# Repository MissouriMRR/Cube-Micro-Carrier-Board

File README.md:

# Cube-Micro-Carrier-Board
Attempt at making a stacking Cube carrier board. The goal is to have the board be the same area as the cube

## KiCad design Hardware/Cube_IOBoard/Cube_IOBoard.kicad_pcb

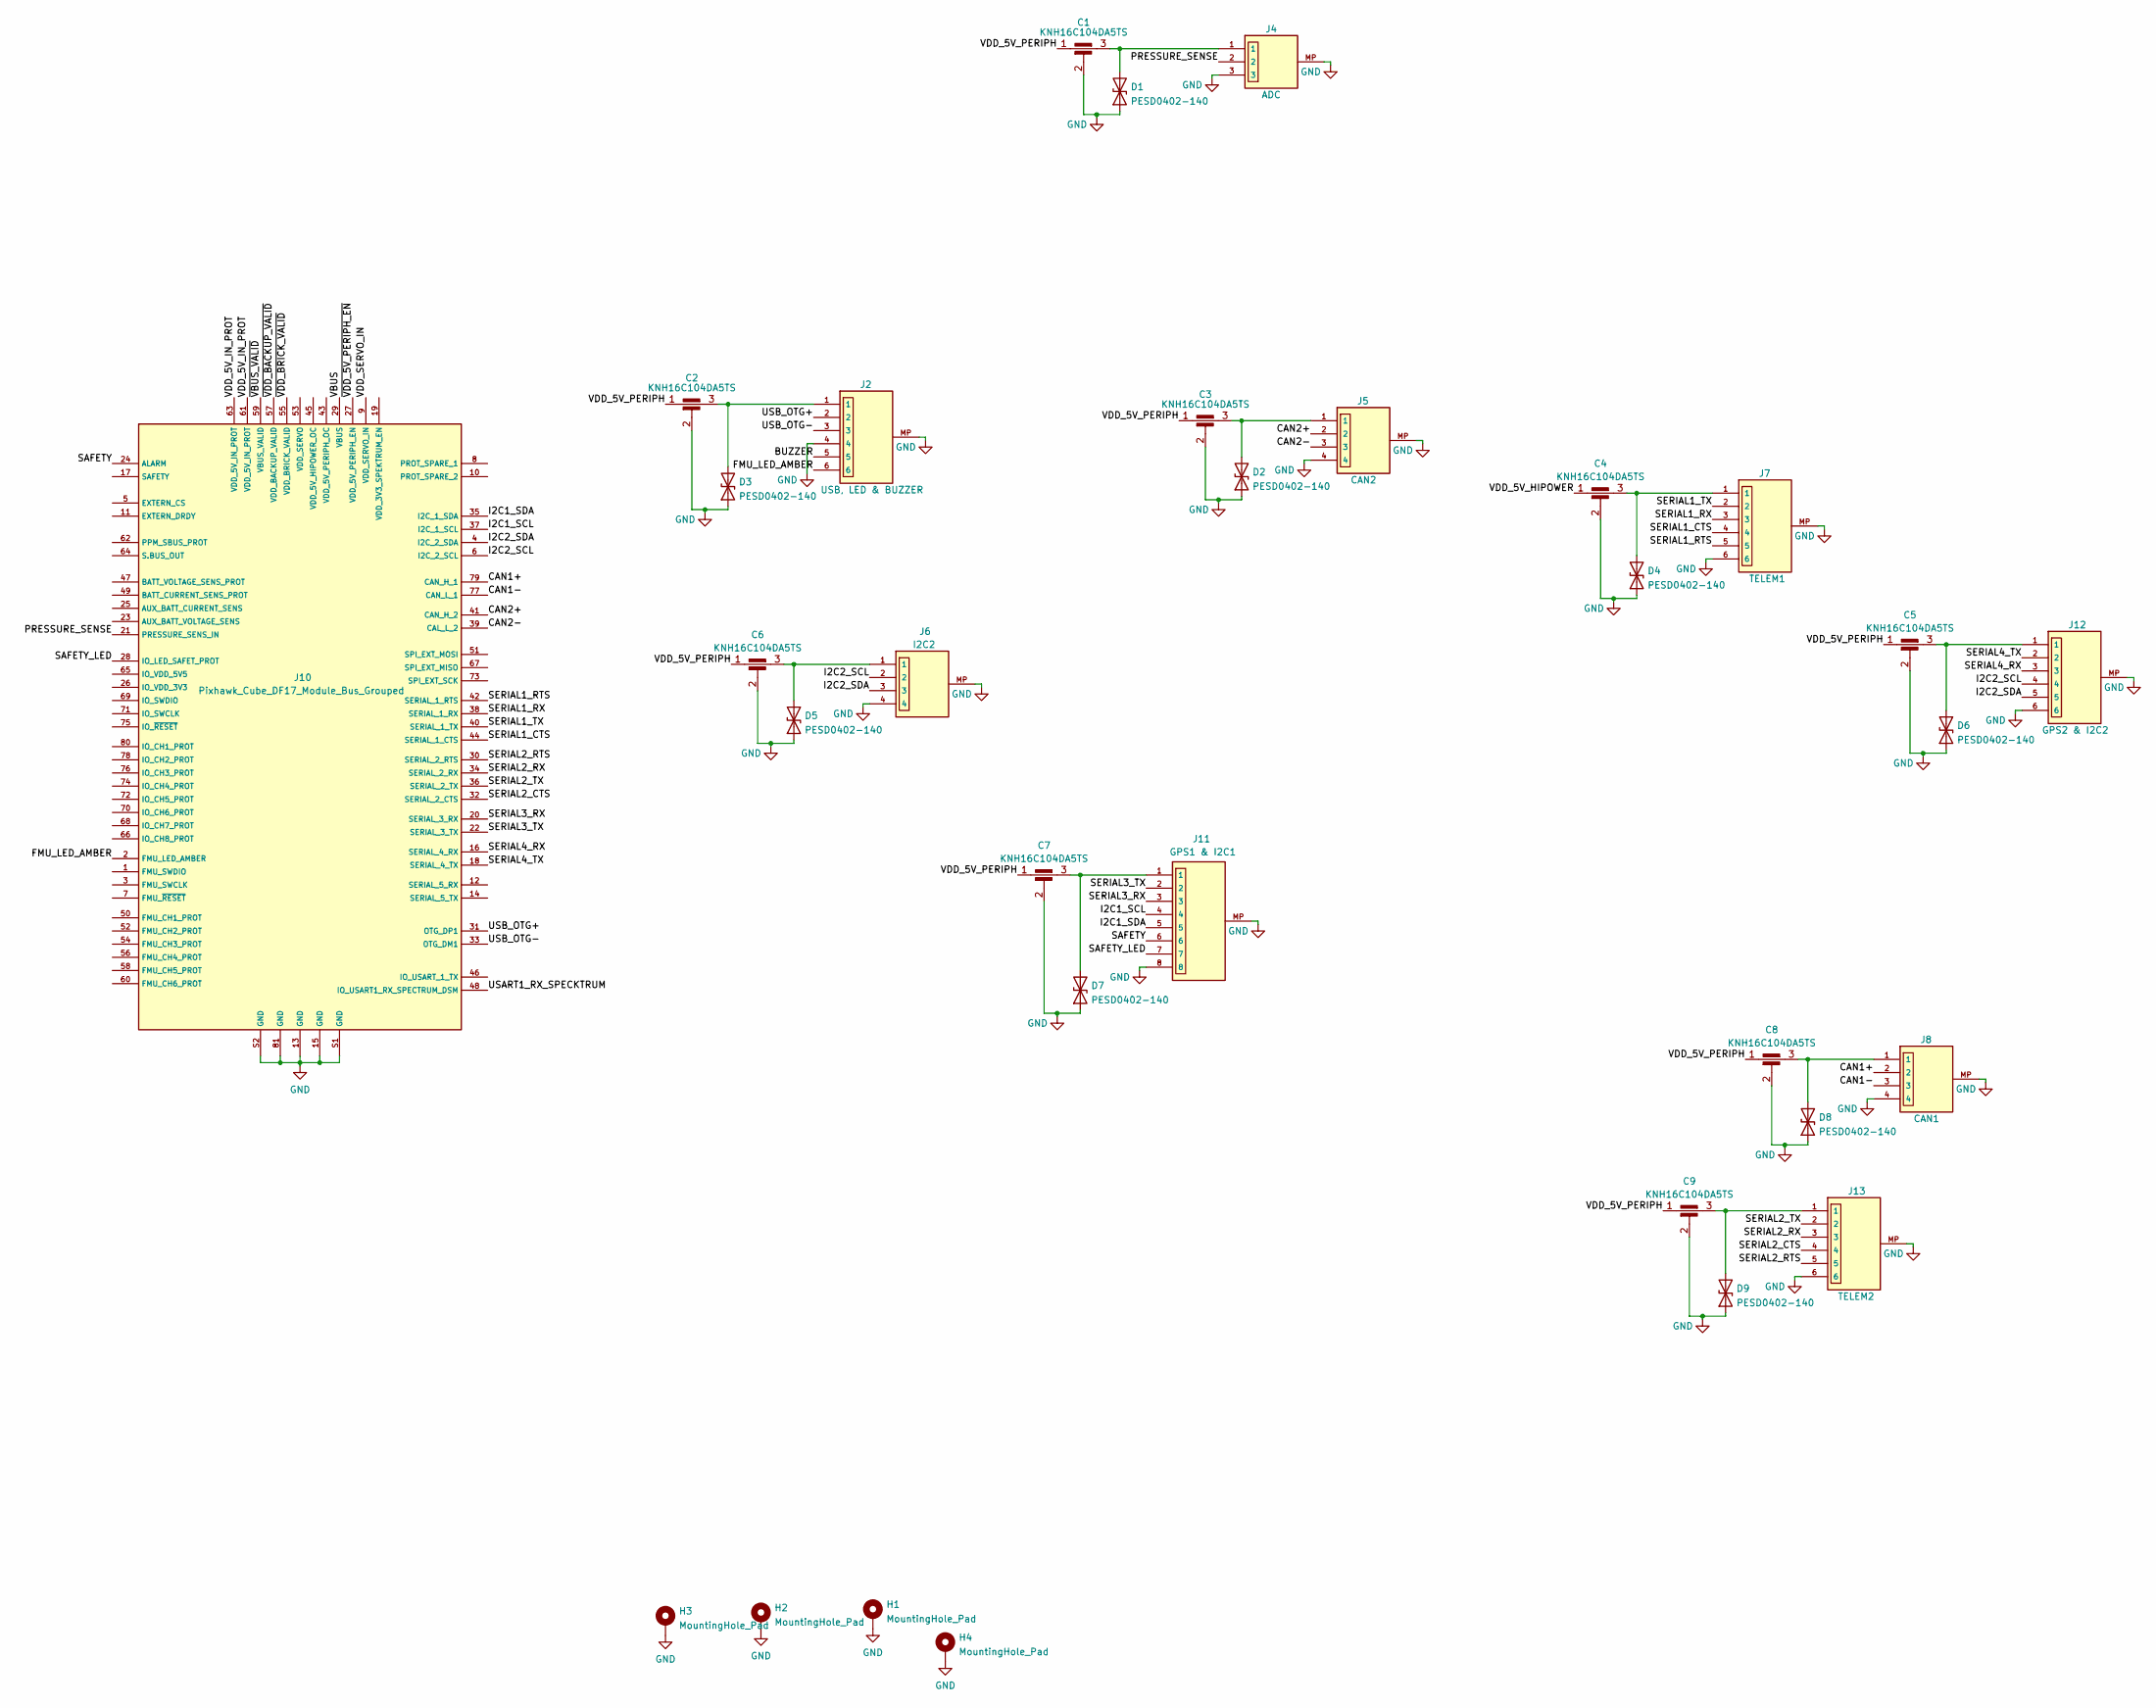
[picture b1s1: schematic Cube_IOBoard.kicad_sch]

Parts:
C1, C2, C3, C4, C5, C6, C7, C8, C9: KNH16C104DA5TS
D1, D2, D3, D4, D5, D6, D7, D8, D9: PESD0402-140; D_0402_1005Metric
H1, H2, H3, H4: MountingHole_Pad; MountingHole_3.2mm_M3_DIN965_Pad
J2: USB, LED & BUZZER; JST_GH_SM06B-GHS-TB_1x06-1MP_P1.25mm_Horizontal; PARTREV N/A
J4: ADC; JST_GH_SM03B-GHS-TB_1x03-1MP_P1.25mm_Horizontal
J5: CAN2; JST_GH_SM04B-GHS-TB_1x04-1MP_P1.25mm_Horizontal; PARTREV N/A
J6: I2C2; JST_GH_SM04B-GHS-TB_1x04-1MP_P1.25mm_Horizontal; PARTREV N/A
J7: TELEM1; JST_GH_SM06B-GHS-TB_1x06-1MP_P1.25mm_Horizontal; PARTREV N/A
J8: CAN1; JST_GH_SM04B-GHS-TB_1x04-1MP_P1.25mm_Horizontal; PARTREV N/A
J10: Pixhawk_Cube_DF17_Module_Bus_Grouped; Cube_DF17_Module_Bus
J11: GPS1 & I2C1; JST_GH_SM08B-GHS-TB_1x08-1MP_P1.25mm_Horizontal
J12: GPS2 & I2C2; JST_GH_SM06B-GHS-TB_1x06-1MP_P1.25mm_Horizontal; PARTREV N/A
J13: TELEM2; JST_GH_SM06B-GHS-TB_1x06-1MP_P1.25mm_Horizontal; PARTREV N/A

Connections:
/BUZZER: J2.5
/CAN1+: J8.2, J10.79 (CAN_H_1)
/CAN1-: J8.3, J10.77 (CAN_L_1)
/CAN2+: J5.2, J10.41 (CAN_H_2)
/CAN2-: J5.3, J10.39 (CAL_L_2)
/FMU_LED_AMBER: J2.6, J10.2 (FMU_LED_AMBER)
/I2C1_SCL: J10.37 (I2C_1_SCL), J11.4
/I2C1_SDA: J10.35 (I2C_1_SDA), J11.5
/I2C2_SCL: J6.2, J10.6 (I2C_2_SCL), J12.4
/I2C2_SDA: J6.3, J10.4 (I2C_2_SDA), J12.5
/PRESSURE_SENSE: J4.2, J10.21 (PRESSURE_SENS_IN)
/SAFETY: J10.24 (ALARM), J11.6
/SAFETY_LED: J10.28 (IO_LED_SAFET_PROT), J11.7
/SERIAL1_CTS: J7.4, J10.44 (SERIAL_1_CTS)
/SERIAL1_RTS: J7.5, J10.42 (SERIAL_1_RTS)
/SERIAL1_RX: J7.3, J10.38 (SERIAL_1_RX)
/SERIAL1_TX: J7.2, J10.40 (SERIAL_1_TX)
/SERIAL2_CTS: J10.32 (SERIAL_2_CTS), J13.4
/SERIAL2_RTS: J10.30 (SERIAL_2_RTS), J13.5
/SERIAL2_RX: J10.34 (SERIAL_2_RX), J13.3
/SERIAL2_TX: J10.36 (SERIAL_2_TX), J13.2
/SERIAL3_RX: J10.20 (SERIAL_3_RX), J11.3
/SERIAL3_TX: J10.22 (SERIAL_3_TX), J11.2
/SERIAL4_RX: J10.16 (SERIAL_4_RX), J12.3
/SERIAL4_TX: J10.18 (SERIAL_4_TX), J12.2
/USART1_RX_SPECKTRUM: J10.48 (IO_USART1_RX_SPECTRUM_DSM)
/USB_OTG+: J2.2, J10.31 (OTG_DP1)
/USB_OTG-: J2.3, J10.33 (OTG_DM1)
/VBUS: J10.29 (VBUS)
/VDD_5V_HIPOWER: C4.1
/VDD_5V_IN_PROT: J10.61 (VDD_5V_IN_PROT), J10.63 (VDD_5V_IN_PROT)
/VDD_5V_PERIPH: C1.1, C2.1, C3.1, C5.1, C6.1, C7.1, C8.1, C9.1
/VDD_SERVO_IN: J10.9 (VDD_SERVO_IN)
/~VBUS_VALID: J10.59 (VBUS_VALID)
/~VDD_5V_PERIPH_EN: J10.27 (VDD_5V_PERIPH_EN)
/~VDD_BACKUP_VALID: J10.57 (VDD_BACKUP_VALID)
/~VDD_BRICK_VALID: J10.55 (VDD_BRICK_VALID)
GND: C1.2, C2.2, C3.2, C4.2, C5.2, C6.2, C7.2, C8.2, C9.2, D1.1 (A1), D2.1 (A1), D3.1 (A1), D4.1 (A1), D5.1 (A1), D6.1 (A1), D7.1 (A1), D8.1 (A1), D9.1 (A1), H1.1, H2.1, H3.1, H4.1, J2.4, J2.MP, J4.3, J4.MP, J5.4, J5.MP, J6.4, J6.MP, J7.6, J7.MP, J8.4, J8.MP, J10.13 (GND), J10.15 (GND), J10.81 (GND), J10.S1 (GND), J10.S2 (GND), J11.8, J11.MP, J12.6, J12.MP, J13.6, J13.MP
unnamed: C2.3, D3.2 (A2), J2.1
unnamed: C1.3, D1.2 (A2), J4.1
unnamed: C3.3, D2.2 (A2), J5.1
unnamed: C6.3, D5.2 (A2), J6.1
unnamed: C4.3, D4.2 (A2), J7.1
unnamed: C8.3, D8.2 (A2), J8.1
unnamed: C7.3, D7.2 (A2), J11.1
unnamed: C5.3, D6.2 (A2), J12.1
unnamed: C9.3, D9.2 (A2), J13.1

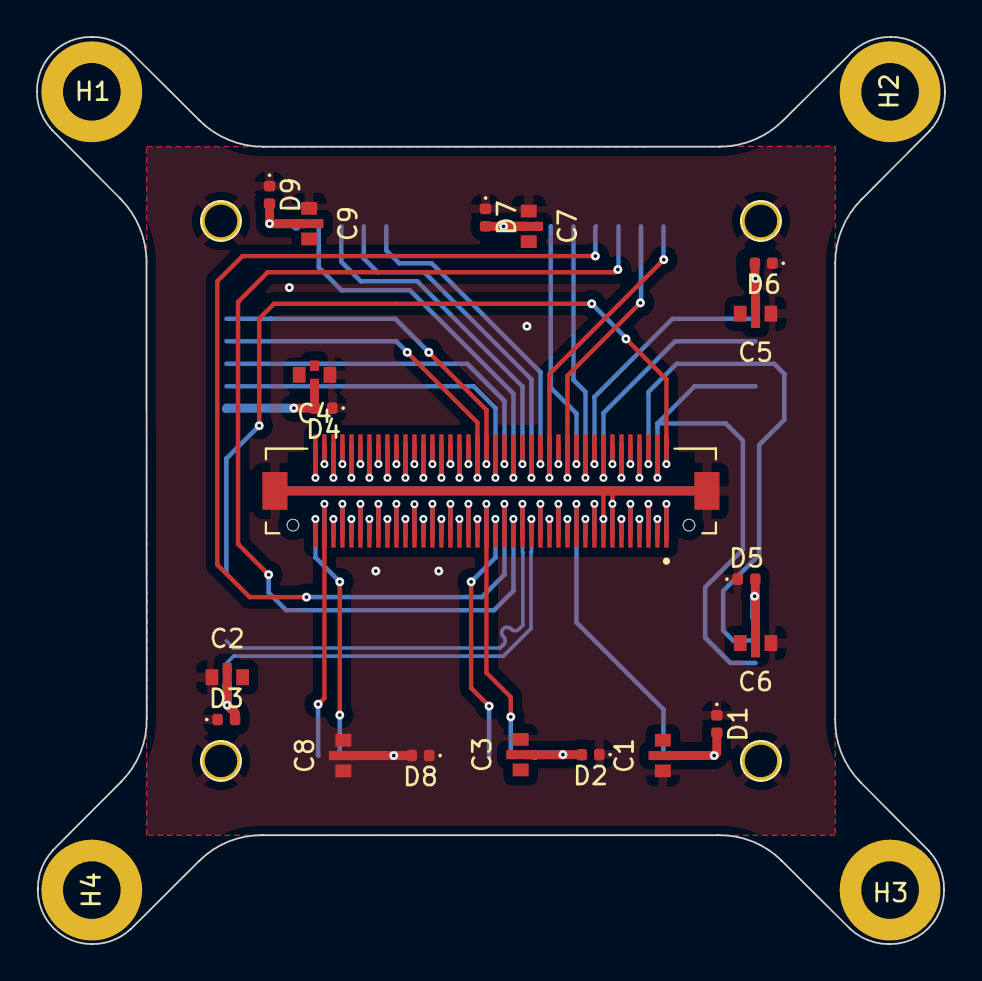
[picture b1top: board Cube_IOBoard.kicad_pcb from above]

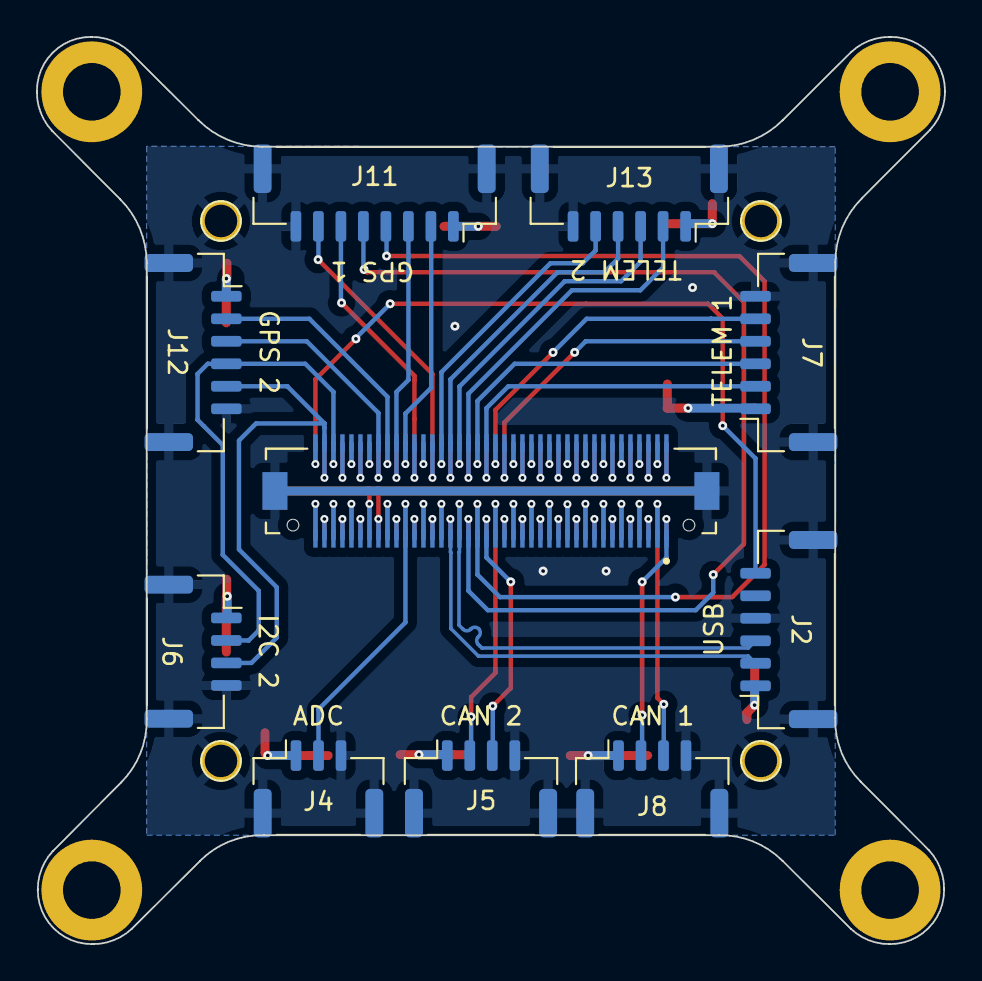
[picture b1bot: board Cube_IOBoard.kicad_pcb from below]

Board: 2 copper layers, 50.5 x 50.4 mm, 32 parts (9 on the bottom side), 38 nets.

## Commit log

2022-11-05 Created project and DF17 symbols
2022-11-05 Created footprint for Cube
2022-11-05 Added servo and power connectors
2022-11-05 Footprints & Symbols for JST & Molex connectors
2022-11-06 Remade Power Supply Module Schematic in KiCAD
    All components labeled with correct values, part numbers, footprints
2022-11-06 Fixed some footprints
2022-11-14 Added ESC Project Files
2022-11-15 Created cube IO module project, schematic, outline
2022-11-15 Added labels to the connectors
2022-11-15 Corrected some schematic symbols
2022-11-27 Added EMI filters and TVS to IO schematic, experimenting with spice sims
2022-11-27 Arranged and routed IO connectors
    It looks like the VDD 5V Periph is supposed to come from the PSM, either I add pins to connect to a separate module or the entire PSM needs to be implemented on this board...**gulp**
2022-12-01 Initial power distribution board
